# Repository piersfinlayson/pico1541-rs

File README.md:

# pico1541

The pico1541 project re-implements the Commodore USB interface (the xum1541) for the Raspberry Pi Pico, and in Rust, using the [`Embassy`](https://github.com/embassy-rs/embassy) project.

The project is currently a work in progress, with the initial aim being to replicate the existing xum1541 functionality.

If you want to contribute to the project, contact the owner at <piers@piers.rocks>.

## Why the pico1541?

The Raspberry Pi brings much higher processing power to the pico1541, making it feasible to additional features and functionality to the traditional xum1541 device, such as
* a WiFi interface
* an in-memory cache.

It can also be migrated more easily to future even higher spec Raspberry Pi based hardware, such as the Pico 2.

The pico1541 aims to be able to operate in fully xum1541 backwards compatible mode, providing identical runtime functionality and performance to the ATMEGA based xum1541.  This allows the pico1541 to be a drop-in replacement for the xum1541, and operate with all existing tooling, including the [OpenCBM](https://github.com/OpenCBM/OpenCBM) cbm* commands, nibtools, etc.

However, it will also be possible to run the pico1541 in a higher functionality, non-backwards compatible, mode which adds additional capabilities, including more robust error handling.

## xum1541 vs pico1541

| Feature | xum1541 | pico1541 |
|---------|---------|----------|
| Processor | ATMEGA32u2 | RP2040 |
| Clock Speed | 16 MHz | 125 MHz |
| Memory | 8 KB SRAM | 264 KB SRAM |
| Flash Storage | 32 KB | 2 MB |
| Connectivity | USB | USB + WiFi* |
| In-memory cache | No | Yes* |
| Enhanced error handling | No | Yes* |
| OpenCBM compatibility | Full | Full† |
| Future expandability | Medium | High |

*In enhanced mode.  WiFi requires Pico W.
†In compatibility mode

## Why [`Embassy`](https://github.com/embassy-rs/embassy)?

To quote:

> The Rust programming language is blazingly fast and memory-efficient, with no runtime, garbage collector or OS. It catches a wide variety of bugs at compile time, thanks to its full memory- and thread-safety, and expressive type system.

> Rust's async/await allows for unprecedentedly easy and efficient multitasking in embedded systems. Tasks get transformed at compile time into state machines that get run cooperatively. It requires no dynamic memory allocation, and runs on a single stack, so no per-task stack size tuning is required. It obsoletes the need for a traditional RTOS with kernel context switching, and is faster and smaller than one!

## Quick Start

If you already have Rust, probe-rs, Rust RP2040 target support (thumbv6m-none-eabi) and the various required build tools installed, all you need to do to build, flash and run this firmware for the Pico (1) to operate in xum1541 compatibility-mode is:

```bash
git clone https://github.com/piersfinlayson/pico1541-rs
cd pico1541-rs
./build.sh xum1541 pico
```

That's it - the pico1541 will now be up and running and connected to the USB bus, presenting itself as an xum1541.  See [`pcb/pico1541_schematic.pdf`](pcb/pico1541_schematic.pdf) for the pins used by this configuration.

For more instructions on building and running, see [BUILD.md](BUILD.md).

## License

pico1541-rs is licensed under the GPL Version 3.  See [LICENSE](LICENSE).

The GPLv3 was chosen to be compatible with the xum1541, which is licensed under the GPLv2 or later license.

## Acknowledgements

The author acknowledges the work of the authors of [OpenCBM](https://github.com/OpenCBM/OpenCBM) and [xum1541](http://www.root.org/~nate/c64/xum1541/), Spiro Trikaliotis and Nate Lawson, on which much of the protocol handling support of pico1541-rs is based.

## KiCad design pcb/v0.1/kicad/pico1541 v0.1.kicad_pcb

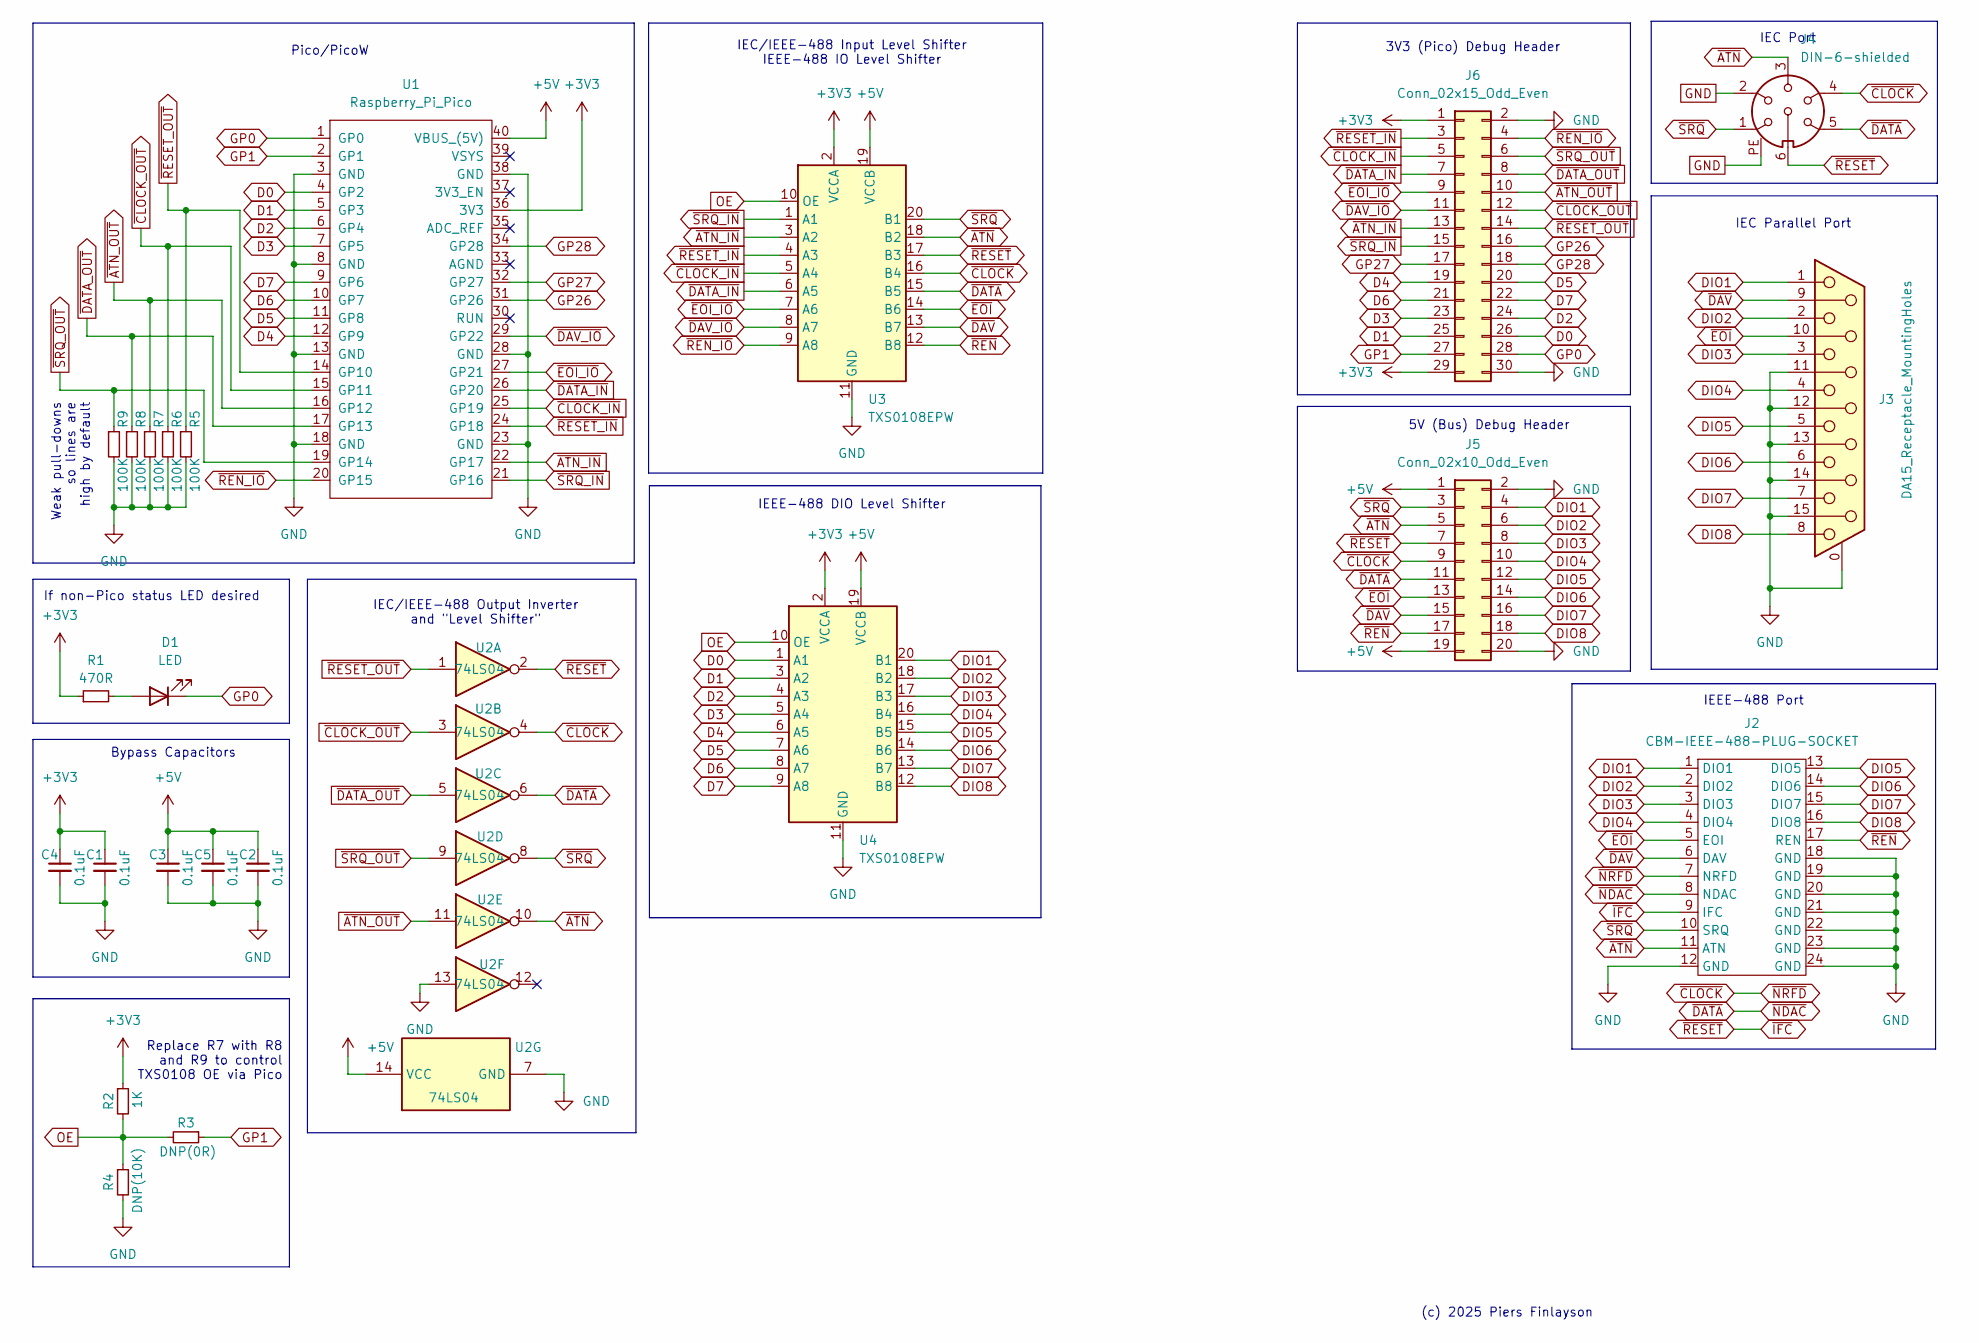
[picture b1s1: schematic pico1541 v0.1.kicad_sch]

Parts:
C1, C2, C3, C4, C5: 0.1uF; C_0603_1608Metric
D1: LED; LED_0603_1608Metric
J2: CBM-IEEE-488-PLUG-SOCKET; centronics_57-24p_right_angle_pcb_connector_female
J3: DA15_Receptacle_MountingHoles; DSUB-15_Female_Horizontal_P2.77x2.84mm_EdgePinOffset7.70mm_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
J4: DIN-6-shielded; DIN_6_ali_express_c64_numbering
J5: Conn_02x10_Odd_Even; PinHeader_2x10_P2.54mm_Vertical
J6: Conn_02x15_Odd_Even; PinHeader_2x15_P2.54mm_Vertical
R1: 470R; R_0603_1608Metric_Pad0.98x0.95mm_HandSolder
R2: 1K; R_0603_1608Metric_Pad0.98x0.95mm_HandSolder
R3: DNP(0R); R_0603_1608Metric_Pad0.98x0.95mm_HandSolder
R4: DNP(10K); R_0603_1608Metric_Pad0.98x0.95mm_HandSolder
R5, R6, R7, R8, R9: 100K; R_0603_1608Metric_Pad0.98x0.95mm_HandSolder
U1: Raspberry_Pi_Pico; Pico_Header
U2: 74LS04; SOIC-14_3.9x8.7mm_P1.27mm
U3, U4: TXS0108EPW; TSSOP-20_4.4x6.5mm_P0.65mm

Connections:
+3V3: C1.1, C4.1, J6.1, J6.29, R1.1, R2.1, U1.36 (3V3), U3.2 (VCCA), U4.2 (VCCA)
+5V: C2.1, C3.1, C5.1, J5.1, J5.19, U1.40 (VBUS_(5V)), U2.14 (VCC), U3.19 (VCCB), U4.19 (VCCB)
D0: J6.26, U1.4 (GP2), U4.1 (A1)
D1: J6.25, U1.5 (GP3), U4.3 (A2)
D2: J6.24, U1.6 (GP4), U4.4 (A3)
D3: J6.23, U1.7 (GP5), U4.5 (A4)
D4: J6.19, U1.12 (GP9), U4.6 (A5)
D5: J6.20, U1.11 (GP8), U4.7 (A6)
D6: J6.21, U1.10 (GP7), U4.8 (A7)
D7: J6.22, U1.9 (GP6), U4.9 (A8)
DIO1: J2.1 (DIO1), J3.1, J5.4, U4.20 (B1)
DIO2: J2.2 (DIO2), J3.2, J5.6, U4.18 (B2)
DIO3: J2.3 (DIO3), J3.3, J5.8, U4.17 (B3)
DIO4: J2.4 (DIO4), J3.4, J5.10, U4.16 (B4)
DIO5: J2.13 (DIO5), J3.5, J5.12, U4.15 (B5)
DIO6: J2.14 (DIO6), J3.6, J5.14, U4.14 (B6)
DIO7: J2.15 (DIO7), J3.7, J5.16, U4.13 (B7)
DIO8: J2.16 (DIO8), J3.8, J5.18, U4.12 (B8)
GND: C1.2, C2.2, C3.2, C4.2, C5.2, J2.12 (GND), J2.18 (GND), J2.19 (GND), J2.20 (GND), J2.21 (GND), J2.22 (GND), J2.23 (GND), J2.24 (GND), J3.0 (PAD), J3.11 (P111), J3.12, J3.13, J3.14, J3.15, J4.2, J4.PE, J5.2, J5.20, J6.2, J6.30, R4.2, R5.2, R6.2, R7.2, R8.2, R9.2, U1.3 (GND), U1.8 (GND), U1.13 (GND), U1.18 (GND), U1.23 (GND), U1.28 (GND), U1.38 (GND), U2.7 (GND), U2.13, U3.11 (GND), U4.11 (GND)
GP0: D1.1 (K), J6.28, U1.1 (GP0)
GP1: J6.27, R3.1, U1.2 (GP1)
GP26: J6.16, U1.31 (GP26)
GP27: J6.17, U1.32 (GP27)
GP28: J6.18, U1.34 (GP28)
unnamed: D1.2 (A), R1.2
OE: R2.2, R3.2, R4.1, U3.10 (OE), U4.10 (OE)
~ATN_IN: J6.13, U1.22 (GP17), U3.3 (A2)
~ATN_OUT: J6.10, R7.1, U1.16 (GP12), U2.11
~ATN: J2.11 (ATN), J4.3, J5.5, U2.10, U3.18 (B2)
~CLOCK_IN: J6.5, U1.25 (GP19), U3.5 (A4)
~CLOCK_OUT: J6.12, R6.1, U1.15 (GP11), U2.3
~CLOCK: J2.7 (NRFD), J4.4, J5.9, U2.4, U3.16 (B4)
~DATA_IN: J6.7, U1.26 (GP20), U3.6 (A5)
~DATA_OUT: J6.8, R8.1, U1.17 (GP13), U2.5
~DATA: J2.8 (NDAC), J4.5, J5.11, U2.6, U3.15 (B5)
~DAV_IO: J6.11, U1.29 (GP22), U3.8 (A7)
~DAV: J2.6 (DAV), J3.9, J5.15, U3.13 (B7)
~EOI_IO: J6.9, U1.27 (GP21), U3.7 (A6)
~EOI: J2.5 (EOI), J3.10, J5.13, U3.14 (B6)
~IFC: J2.9 (IFC), J4.6, J5.7, U2.2, U3.17 (B3)
~REN_IO: J6.4, U1.20 (GP15), U3.9 (A8)
~REN: J2.17 (REN), J5.17, U3.12 (B8)
~RESET_IN: J6.3, U1.24 (GP18), U3.4 (A3)
~RESET_OUT: J6.14, R5.1, U1.14 (GP10), U2.1
~SRQ_IN: J6.15, U1.21 (GP16), U3.1 (A1)
~SRQ_OUT: J6.6, R9.1, U1.19 (GP14), U2.9
~SRQ: J2.10 (SRQ), J4.1, J5.3, U2.8, U3.20 (B1)

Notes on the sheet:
IEC Parallel Port
If non-Pico status LED desired
Weak pull-downs so lines are high by default
(c) 2025 Piers Finlayson
IEC Port
3V3 (Pico) Debug Header
Pico/PicoW
IEEE-488 DIO Level Shifter
5V (Bus) Debug Header
Replace R7 with R8 and R9 to control TXS0108 OE via Pico
IEC/IEEE-488 Input Level Shifter IEEE-488 IO Level Shifter
Bypass Capacitors
IEEE-488 Port
IEC/IEEE-488 Output Inverter and "Level Shifter"

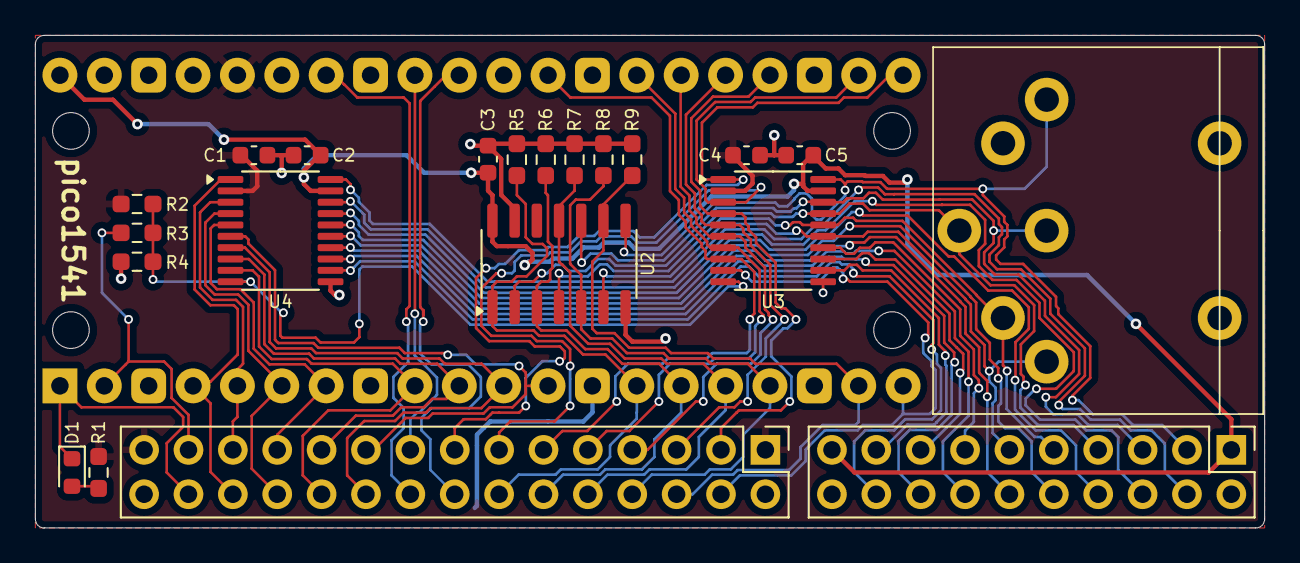
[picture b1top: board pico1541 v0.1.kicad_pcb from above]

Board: 2 copper layers, 70.4 x 28.2 mm, 22 parts (0 on the bottom side), 47 nets.

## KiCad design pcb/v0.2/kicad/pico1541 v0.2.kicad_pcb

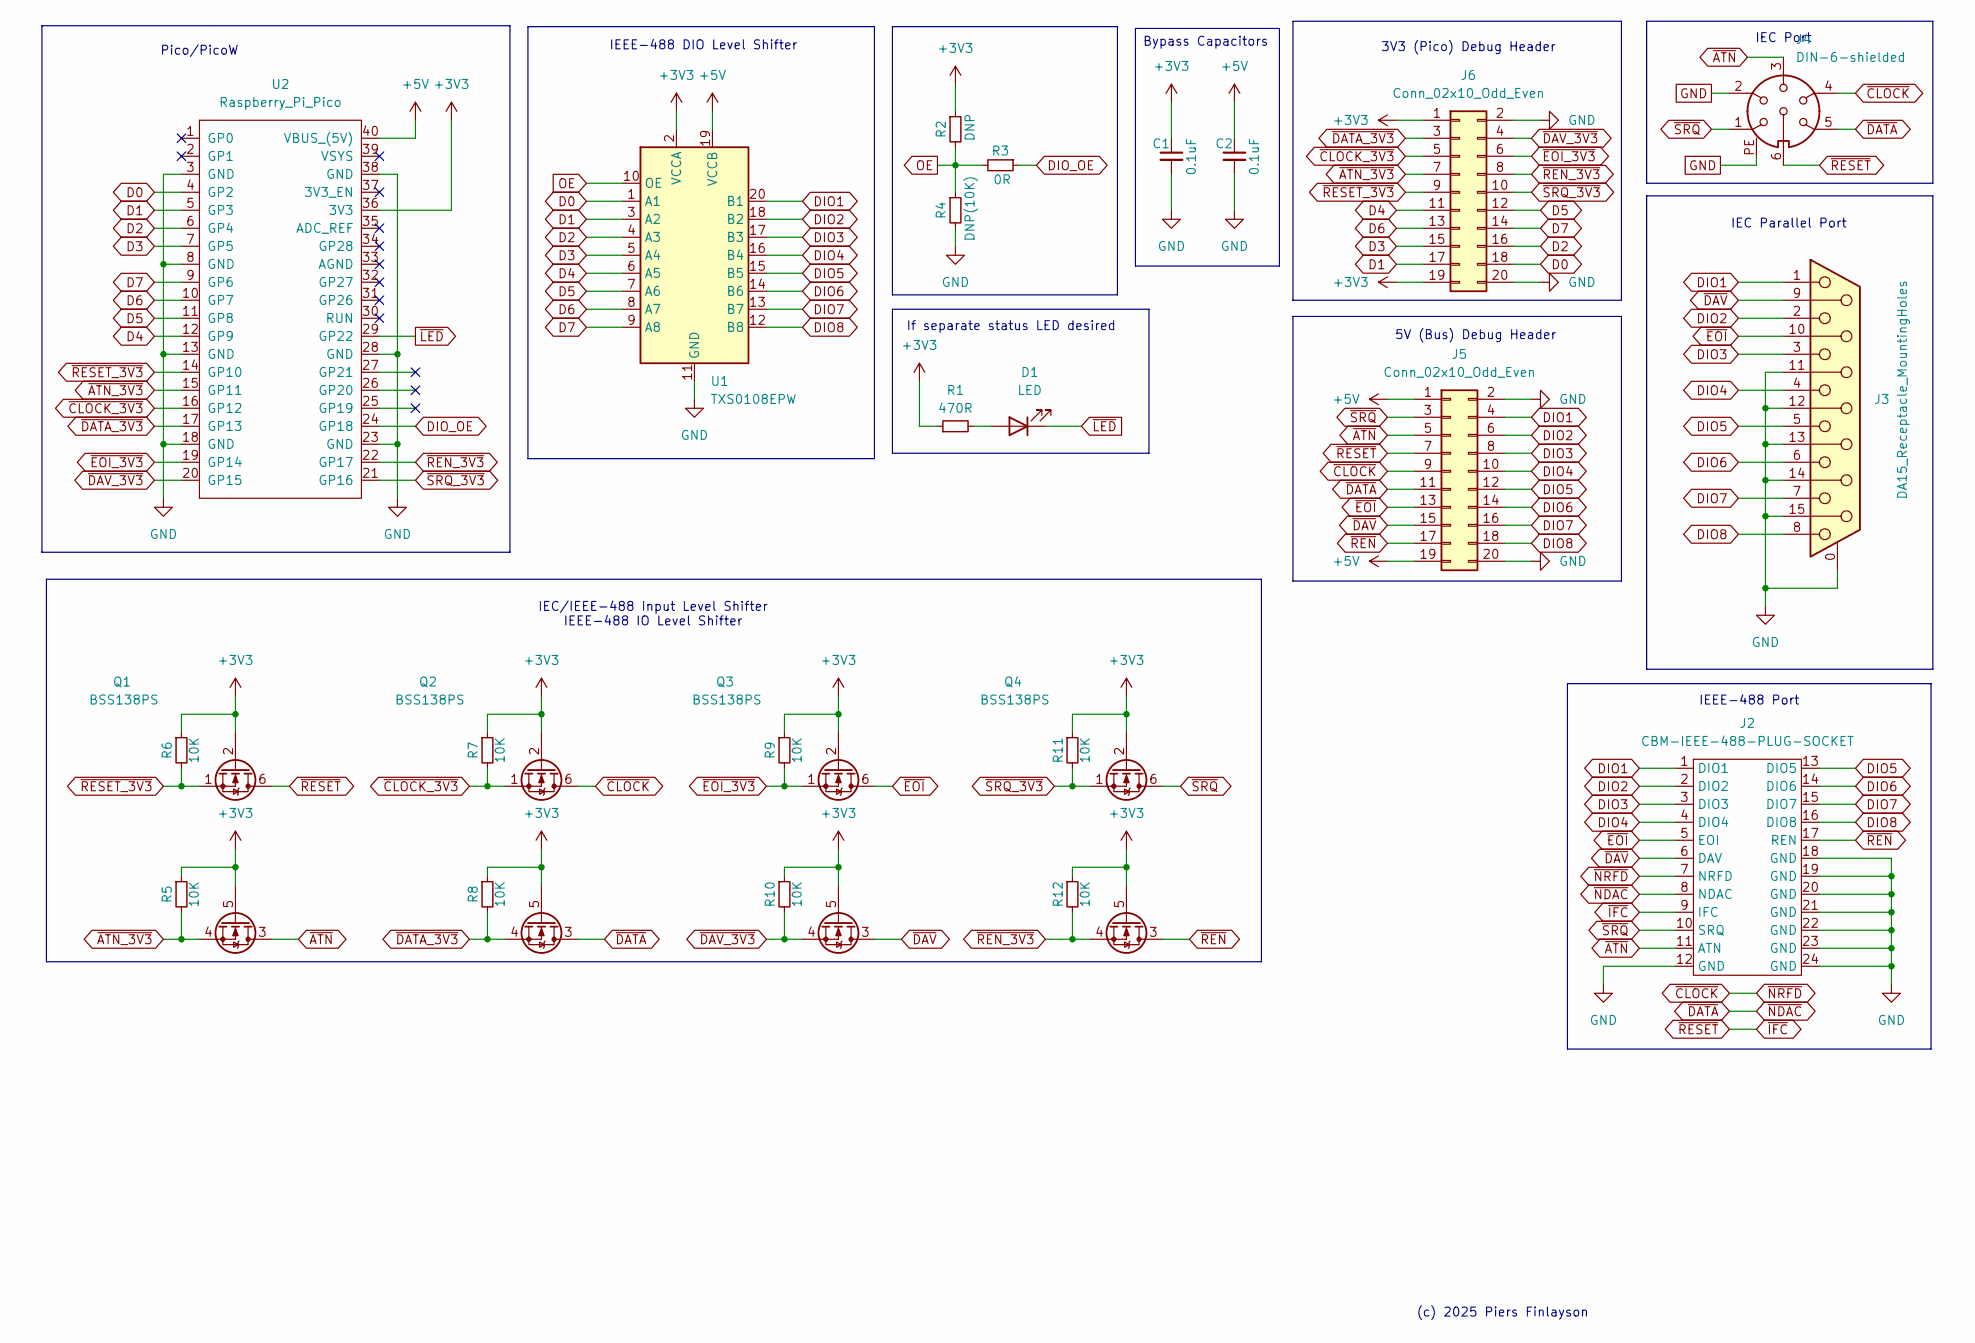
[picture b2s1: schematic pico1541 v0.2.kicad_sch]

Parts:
C1, C2: 0.1uF; C_0603_1608Metric
D1: LED; LED_0603_1608Metric
J2: CBM-IEEE-488-PLUG-SOCKET; centronics_57-24p_right_angle_pcb_connector_female
J3: DA15_Receptacle_MountingHoles; DSUB-15_Female_Horizontal_P2.77x2.84mm_EdgePinOffset7.70mm_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
J4: DIN-6-shielded; DIN_6_ali_express_c64_numbering
J5, J6: Conn_02x10_Odd_Even; PinHeader_2x10_P2.54mm_Vertical
Q1, Q2, Q3, Q4: BSS138PS; SOT-363_SC-70-6
R1: 470R; R_0603_1608Metric_Pad0.98x0.95mm_HandSolder
R2: DNP; R_0603_1608Metric_Pad0.98x0.95mm_HandSolder
R3: 0R; R_0603_1608Metric_Pad0.98x0.95mm_HandSolder
R4: DNP(10K); R_0603_1608Metric_Pad0.98x0.95mm_HandSolder
R5, R6, R7, R8, R9, R10, R11, R12: 10K; R_0603_1608Metric_Pad0.98x0.95mm_HandSolder
U1: TXS0108EPW; TSSOP-20_4.4x6.5mm_P0.65mm
U2: Raspberry_Pi_Pico; Pico_Header

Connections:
+3V3: C1.1, J6.1, J6.19, Q1.2 (G1), Q1.5 (G2), Q2.2 (G1), Q2.5 (G2), Q3.2 (G1), Q3.5 (G2), Q4.2 (G1), Q4.5 (G2), R1.1, R2.1, R5.1, R6.1, R7.1, R8.1, R9.1, R10.1, R11.1, R12.1, U1.2 (VCCA), U2.36 (3V3)
+5V: C2.1, J5.1, J5.19, U1.19 (VCCB), U2.40 (VBUS_(5V))
D0: J6.18, U1.1 (A1), U2.4 (GP2)
D1: J6.17, U1.3 (A2), U2.5 (GP3)
D2: J6.16, U1.4 (A3), U2.6 (GP4)
D3: J6.15, U1.5 (A4), U2.7 (GP5)
D4: J6.11, U1.6 (A5), U2.12 (GP9)
D5: J6.12, U1.7 (A6), U2.11 (GP8)
D6: J6.13, U1.8 (A7), U2.10 (GP7)
D7: J6.14, U1.9 (A8), U2.9 (GP6)
DIO1: J2.1 (DIO1), J3.1, J5.4, U1.20 (B1)
DIO2: J2.2 (DIO2), J3.2, J5.6, U1.18 (B2)
DIO3: J2.3 (DIO3), J3.3, J5.8, U1.17 (B3)
DIO4: J2.4 (DIO4), J3.4, J5.10, U1.16 (B4)
DIO5: J2.13 (DIO5), J3.5, J5.12, U1.15 (B5)
DIO6: J2.14 (DIO6), J3.6, J5.14, U1.14 (B6)
DIO7: J2.15 (DIO7), J3.7, J5.16, U1.13 (B7)
DIO8: J2.16 (DIO8), J3.8, J5.18, U1.12 (B8)
DIO_OE: R3.1, U2.24 (GP18)
GND: C1.2, C2.2, J2.12 (GND), J2.18 (GND), J2.19 (GND), J2.20 (GND), J2.21 (GND), J2.22 (GND), J2.23 (GND), J2.24 (GND), J3.0 (PAD), J3.11 (P111), J3.12, J3.13, J3.14, J3.15, J4.2, J4.PE, J5.2, J5.20, J6.2, J6.20, R4.2, U1.11 (GND), U2.3 (GND), U2.8 (GND), U2.13 (GND), U2.18 (GND), U2.23 (GND), U2.28 (GND), U2.38 (GND)
unnamed: D1.2 (A), R1.2
OE: R2.2, R3.2, R4.1, U1.10 (OE)
~ATN_3V3: J6.7, Q1.4 (S2), R5.2, U2.15 (GP11)
~ATN: J2.11 (ATN), J4.3, J5.5, Q1.3 (D2)
~CLOCK_3V3: J6.5, Q2.1 (S1), R7.2, U2.16 (GP12)
~CLOCK: J2.7 (NRFD), J4.4, J5.9, Q2.6 (D1)
~DATA_3V3: J6.3, Q2.4 (S2), R8.2, U2.17 (GP13)
~DATA: J2.8 (NDAC), J4.5, J5.11, Q2.3 (D2)
~DAV_3V3: J6.4, Q3.4 (S2), R10.2, U2.20 (GP15)
~DAV: J2.6 (DAV), J3.9, J5.15, Q3.3 (D2)
~EOI_3V3: J6.6, Q3.1 (S1), R9.2, U2.19 (GP14)
~EOI: J2.5 (EOI), J3.10, J5.13, Q3.6 (D1)
~IFC: J2.9 (IFC), J4.6, J5.7, Q1.6 (D1)
~LED: D1.1 (K), U2.29 (GP22)
~REN_3V3: J6.8, Q4.4 (S2), R12.2, U2.22 (GP17)
~REN: J2.17 (REN), J5.17, Q4.3 (D2)
~RESET_3V3: J6.9, Q1.1 (S1), R6.2, U2.14 (GP10)
~SRQ_3V3: J6.10, Q4.1 (S1), R11.2, U2.21 (GP16)
~SRQ: J2.10 (SRQ), J4.1, J5.3, Q4.6 (D1)

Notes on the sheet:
IEC Parallel Port
If separate status LED desired
(c) 2025 Piers Finlayson
IEC Port
3V3 (Pico) Debug Header
Pico/PicoW
IEEE-488 DIO Level Shifter
5V (Bus) Debug Header
IEC/IEEE-488 Input Level Shifter IEEE-488 IO Level Shifter
Bypass Capacitors
IEEE-488 Port

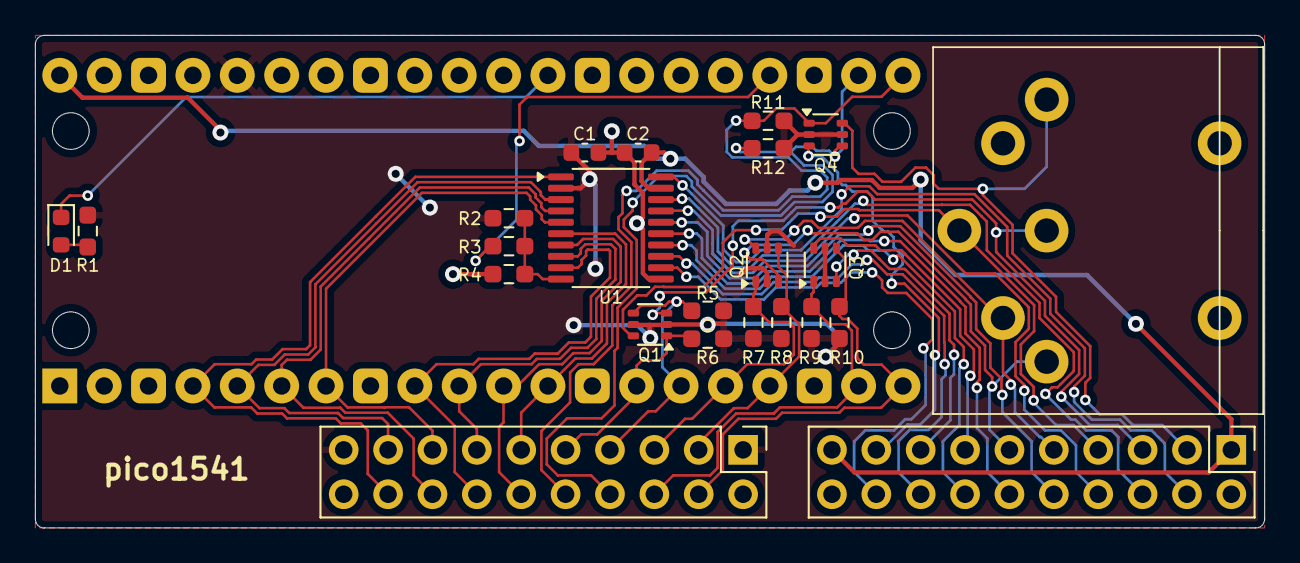
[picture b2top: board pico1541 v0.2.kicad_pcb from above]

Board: 2 copper layers, 70.4 x 28.2 mm, 24 parts (0 on the bottom side), 39 nets.

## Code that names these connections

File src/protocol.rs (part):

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
        // Create the lines
        let clock_line = Line::new(
            self.iec_pins.clock_in,
            self.gpios[self.iec_pins.clock_in as usize].take().unwrap(),
            self.iec_pins.clock_out,
            self.gpios[self.iec_pins.clock_out as usize].take().unwrap(),
        );
        let data_line = Line::new(
            self.iec_pins.data_in,
            self.gpios[self.iec_pins.data_in as usize].take().unwrap(),
            self.iec_pins.data_out,
            self.gpios[self.iec_pins.data_out as usize].take().unwrap(),
        );
        let atn_line = Line::new(
            self.iec_pins.atn_in,
            self.gpios[self.iec_pins.atn_in as usize].take().unwrap(),
            self.iec_pins.atn_out,
            self.gpios[self.iec_pins.atn_out as usize].take().unwrap(),
        );
        let reset_line = Line::new(
            self.iec_pins.reset_in,
            self.gpios[self.iec_pins.reset_in as usize].take().unwrap(),
            self.iec_pins.reset_out,
            self.gpios[self.iec_pins.reset_out as usize].take().unwrap(),
        );
        let srq_line = Line::new(
            self.iec_pins.srq_in,
            self.gpios[self.iec_pins.srq_in as usize].take().unwrap(),
            self.iec_pins.srq_out,
            self.gpios[self.iec_pins.srq_out as usize].take().unwrap(),
        );

        // Create array of Digital IO pins
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
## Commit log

2025-02-25 remove rom.rs
2025-02-25 various refactoring
2025-02-26 refactored lib.rs, added multi-thread capable watchdog, added status display (via led)
2025-02-26 add core 1, cargo fmt and clippy
2025-02-26 hone multi-core approach
2025-02-26 initial iec implementation
2025-02-28 add support for spawning tasks on core 0
2025-02-28 change PROTOCOL_ACTION to a signal
2025-02-28 split Bulk and ProtocolHandler into separate tasks
2025-03-02 use Delay and Timer appropriately
2025-03-02 use delay_yield and delay_block macros
2025-03-02 remove unused crate
2025-03-02 readd portable-atomic, as it's required by static_cell
2025-03-02 change comment
2025-03-02 (finally) get rid of unsafe use of core1_stack
2025-03-02 update read() comment
2025-03-04 lots of refactoring
2025-03-04 substantial gpio rewrite
2025-03-04 make sure we have a driver when we need one
2025-03-04 fix panics
2025-03-04 add some yielding
2025-03-04 add some logging
2025-03-04 remove allow(dead_code)
2025-03-04 fix debug logs
2025-03-05 add protocol handler/driver circular buffer
2025-03-05 get rid of active flag, unnecessary
2025-03-05 improvements
2025-03-05 get usbdatatransfer buffer handling working
2025-03-05 get raw_write working
2025-03-06 improve readability of raw_read and raw_write
2025-03-06 improve readability of functions
2025-03-06 implement other XUM commands
2025-03-07 add pcb schematic and license
2025-03-07 a few fixes
2025-03-07 add pico1541 v0.1 pin mappings
2025-03-07 only send status response if cbm or tap protocols
2025-03-08 start adding more IEC read/write support
2025-03-08 improve comment
2025-03-08 cargo fmt
2025-03-09 quick and dirty led support on pico w
2025-03-10 add better wifi led gpio support
2025-03-10 change logging
2025-03-10 simplify cargo features
2025-03-11 get pico 2 working
2025-03-11 better init handling
2025-03-11 improve logging and get iec working again
2025-03-11 impement pp, p2, s1 and s2 writes
2025-03-12 initial S1 S2 PP P2 read implementations
2025-03-12 improve non cbm read/write fns
2025-03-12 support p1/pp/s1/s2
2025-03-12 improve readme around flashing
2025-03-12 support PP_READ and PP_WRITE commands
2025-03-12 no need to check if built before running - cargo run will build if needed
2025-03-12 sort out read/write errors
2025-03-12 tweak log levels
2025-03-12 make forever duration a sensible value, to avoid panic when adding it to Instant::now()
2025-03-12 better time support, and move entry point functions to own module
2025-03-12 improve logging
2025-03-12 reduce logging level
2025-03-12 continue to tweak loggin
2025-03-12 continue to tweak logging
2025-03-12 yield after spawning tasks to give time for them to start
2025-03-12 change specced power draw
2025-03-12 refactoring and improve logging
2025-03-12 various updates including returning status flags on init
2025-03-12 move watchdog much earlier in boot
2025-03-13 major refactoring and added nib read functions
2025-03-13 move cbm_read into read module and refactor
2025-03-13 improve commenting
2025-03-13 major rework of write routines into own module and combining cbm and non-cbm
2025-03-13 finish refactoring read/write and implement nib protocols
2025-03-14 move to embassy reboot_to_usb_boot, and try to use rp2350 equivalent
2025-03-15 upgrade to 2024 edition
2025-03-17 add source readme
2025-03-17 update portable-atomic
2025-03-28 fix release builds
2025-03-28 add ci.sh
2025-03-28 make executable
2025-03-28 fix pico target
2025-03-28 remove ci.sh
2025-03-28 add jenkins files
2025-04-20 lots of changes
2025-04-20 add clippy
2025-04-20 fix clippy warnings
2025-04-20 make clippy happy
2025-04-21 pander to clippy
2025-04-21 feed clippy
2025-05-12 add hw_tests
2025-05-12 get hw tests running
2025-05-12 register correct task
2025-05-12 get tests working better
2025-05-13 add gerbers
2025-05-13 get back to back testig working
2025-05-13 add test-drive
2025-05-13 add support for IEC protocol bytes
2025-05-14 add more device functionality
2025-05-14 change pull behaviour
2025-05-14 fix log typo
2025-05-14 fix test_drive
2025-05-14 when released, turn output pins to floating inputs
2025-12-09 add kicad pcb files
2025-12-09 fix merge issues

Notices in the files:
src/protocol.rs:
Copyright (c) 2025 Piers Finlayson <piers@piers.rocks>
GPLv3 licensed - see https://www.gnu.org/licenses/gpl-3.0.html
pcb/v0.1/kicad/pico1541 v0.1.kicad_pcb:
(c) 2025 packom.net
